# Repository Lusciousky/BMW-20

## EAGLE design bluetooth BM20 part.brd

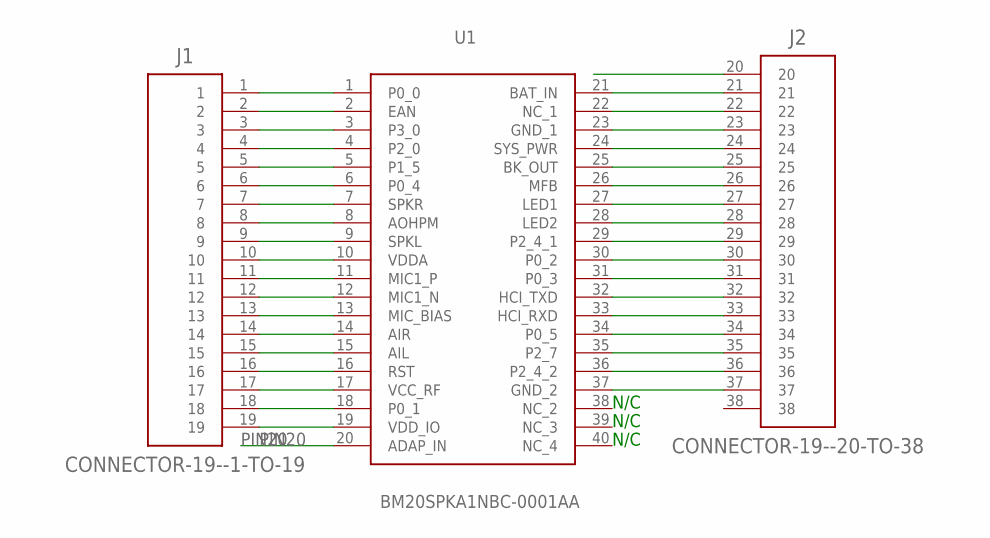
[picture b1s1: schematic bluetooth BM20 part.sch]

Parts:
J1: CONNECTOR-19--1-TO-19; ESQ-119-XX-XX-S
J2: CONNECTOR-19--20-TO-38; ESQ-119-XX-XX-S--PIN-1-ROUND
U1: BM20SPKA1NBC-0001AA; BM20SPKA1NBC0001AA

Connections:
unnamed: J1.4, U1.4 (P2_0)
unnamed: J1.1, U1.1 (P0_0)
unnamed: J1.5, U1.5 (P1_5)
unnamed: J1.2, U1.2 (EAN)
unnamed: J1.6, U1.6 (P0_4)
unnamed: J1.3, U1.3 (P3_0)
unnamed: J1.7, U1.7 (SPKR)
unnamed: J1.8, U1.8 (AOHPM)
unnamed: J1.9, U1.9 (SPKL)
unnamed: J1.10, U1.10 (VDDA)
unnamed: J1.11, U1.11 (MIC1_P)
unnamed: J1.12, U1.12 (MIC1_N)
unnamed: J1.13, U1.13 (MIC_BIAS)
unnamed: J1.14, U1.14 (AIR)
unnamed: J1.15, U1.15 (AIL)
unnamed: J1.16, U1.16 (RST)
unnamed: J1.17, U1.17 (VCC_RF)
unnamed: J1.18, U1.18 (P0_1)
unnamed: J1.19, U1.19 (VDD_IO)
unnamed: J2.23, U1.23 (GND_1)
unnamed: J2.24, U1.24 (SYS_PWR)
unnamed: J2.21, U1.21 (BAT_IN)
unnamed: J2.25, U1.25 (BK_OUT)
unnamed: J2.22, U1.22 (NC_1)
unnamed: J2.26, U1.26 (MFB)
unnamed: J2.27, U1.27 (LED1)
unnamed: J2.28, U1.28 (LED2)
unnamed: J2.29, U1.29 (P2_4_1)
unnamed: J2.30, U1.30 (P0_2)
unnamed: J2.31, U1.31 (P0_3)
unnamed: J2.32, U1.32 (HCI_TXD)
unnamed: J2.33, U1.33 (HCI_RXD)
unnamed: J2.34, U1.34 (P0_5)
unnamed: J2.35, U1.35 (P2_7)
unnamed: J2.36, U1.36 (P2_4_2)
unnamed: J2.37, U1.37 (GND_2)
PIN20: J2.20, U1.20 (ADAP_IN)

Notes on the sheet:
N/C

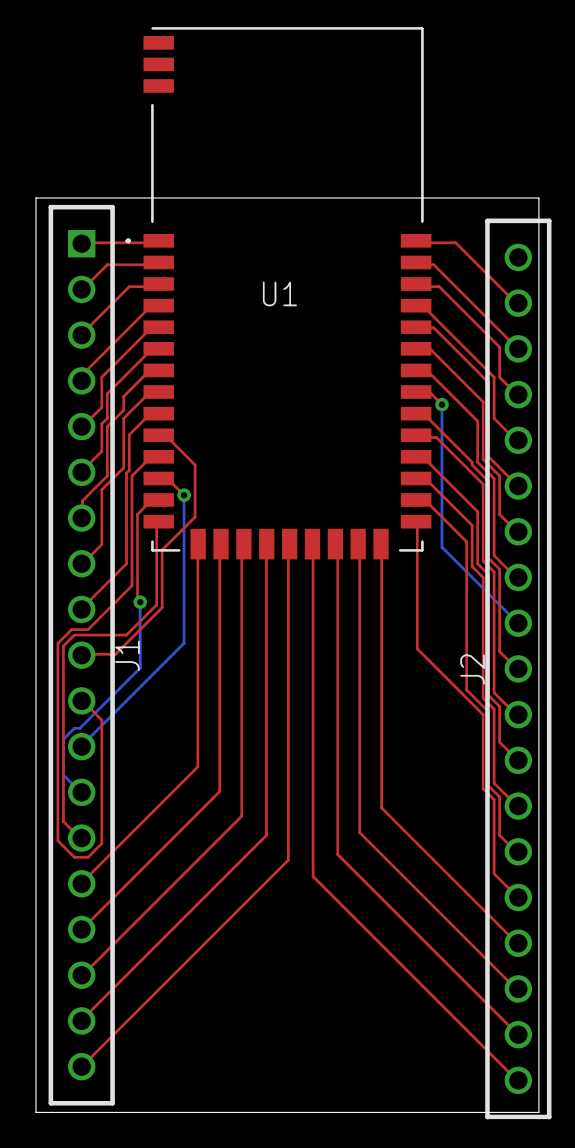
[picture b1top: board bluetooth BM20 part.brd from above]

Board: 2 copper layers, 27.9 x 50.8 mm, 3 parts (0 on the bottom side), 37 nets.

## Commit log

2022-01-27 Add files via upload
    haha, 1st file ever
